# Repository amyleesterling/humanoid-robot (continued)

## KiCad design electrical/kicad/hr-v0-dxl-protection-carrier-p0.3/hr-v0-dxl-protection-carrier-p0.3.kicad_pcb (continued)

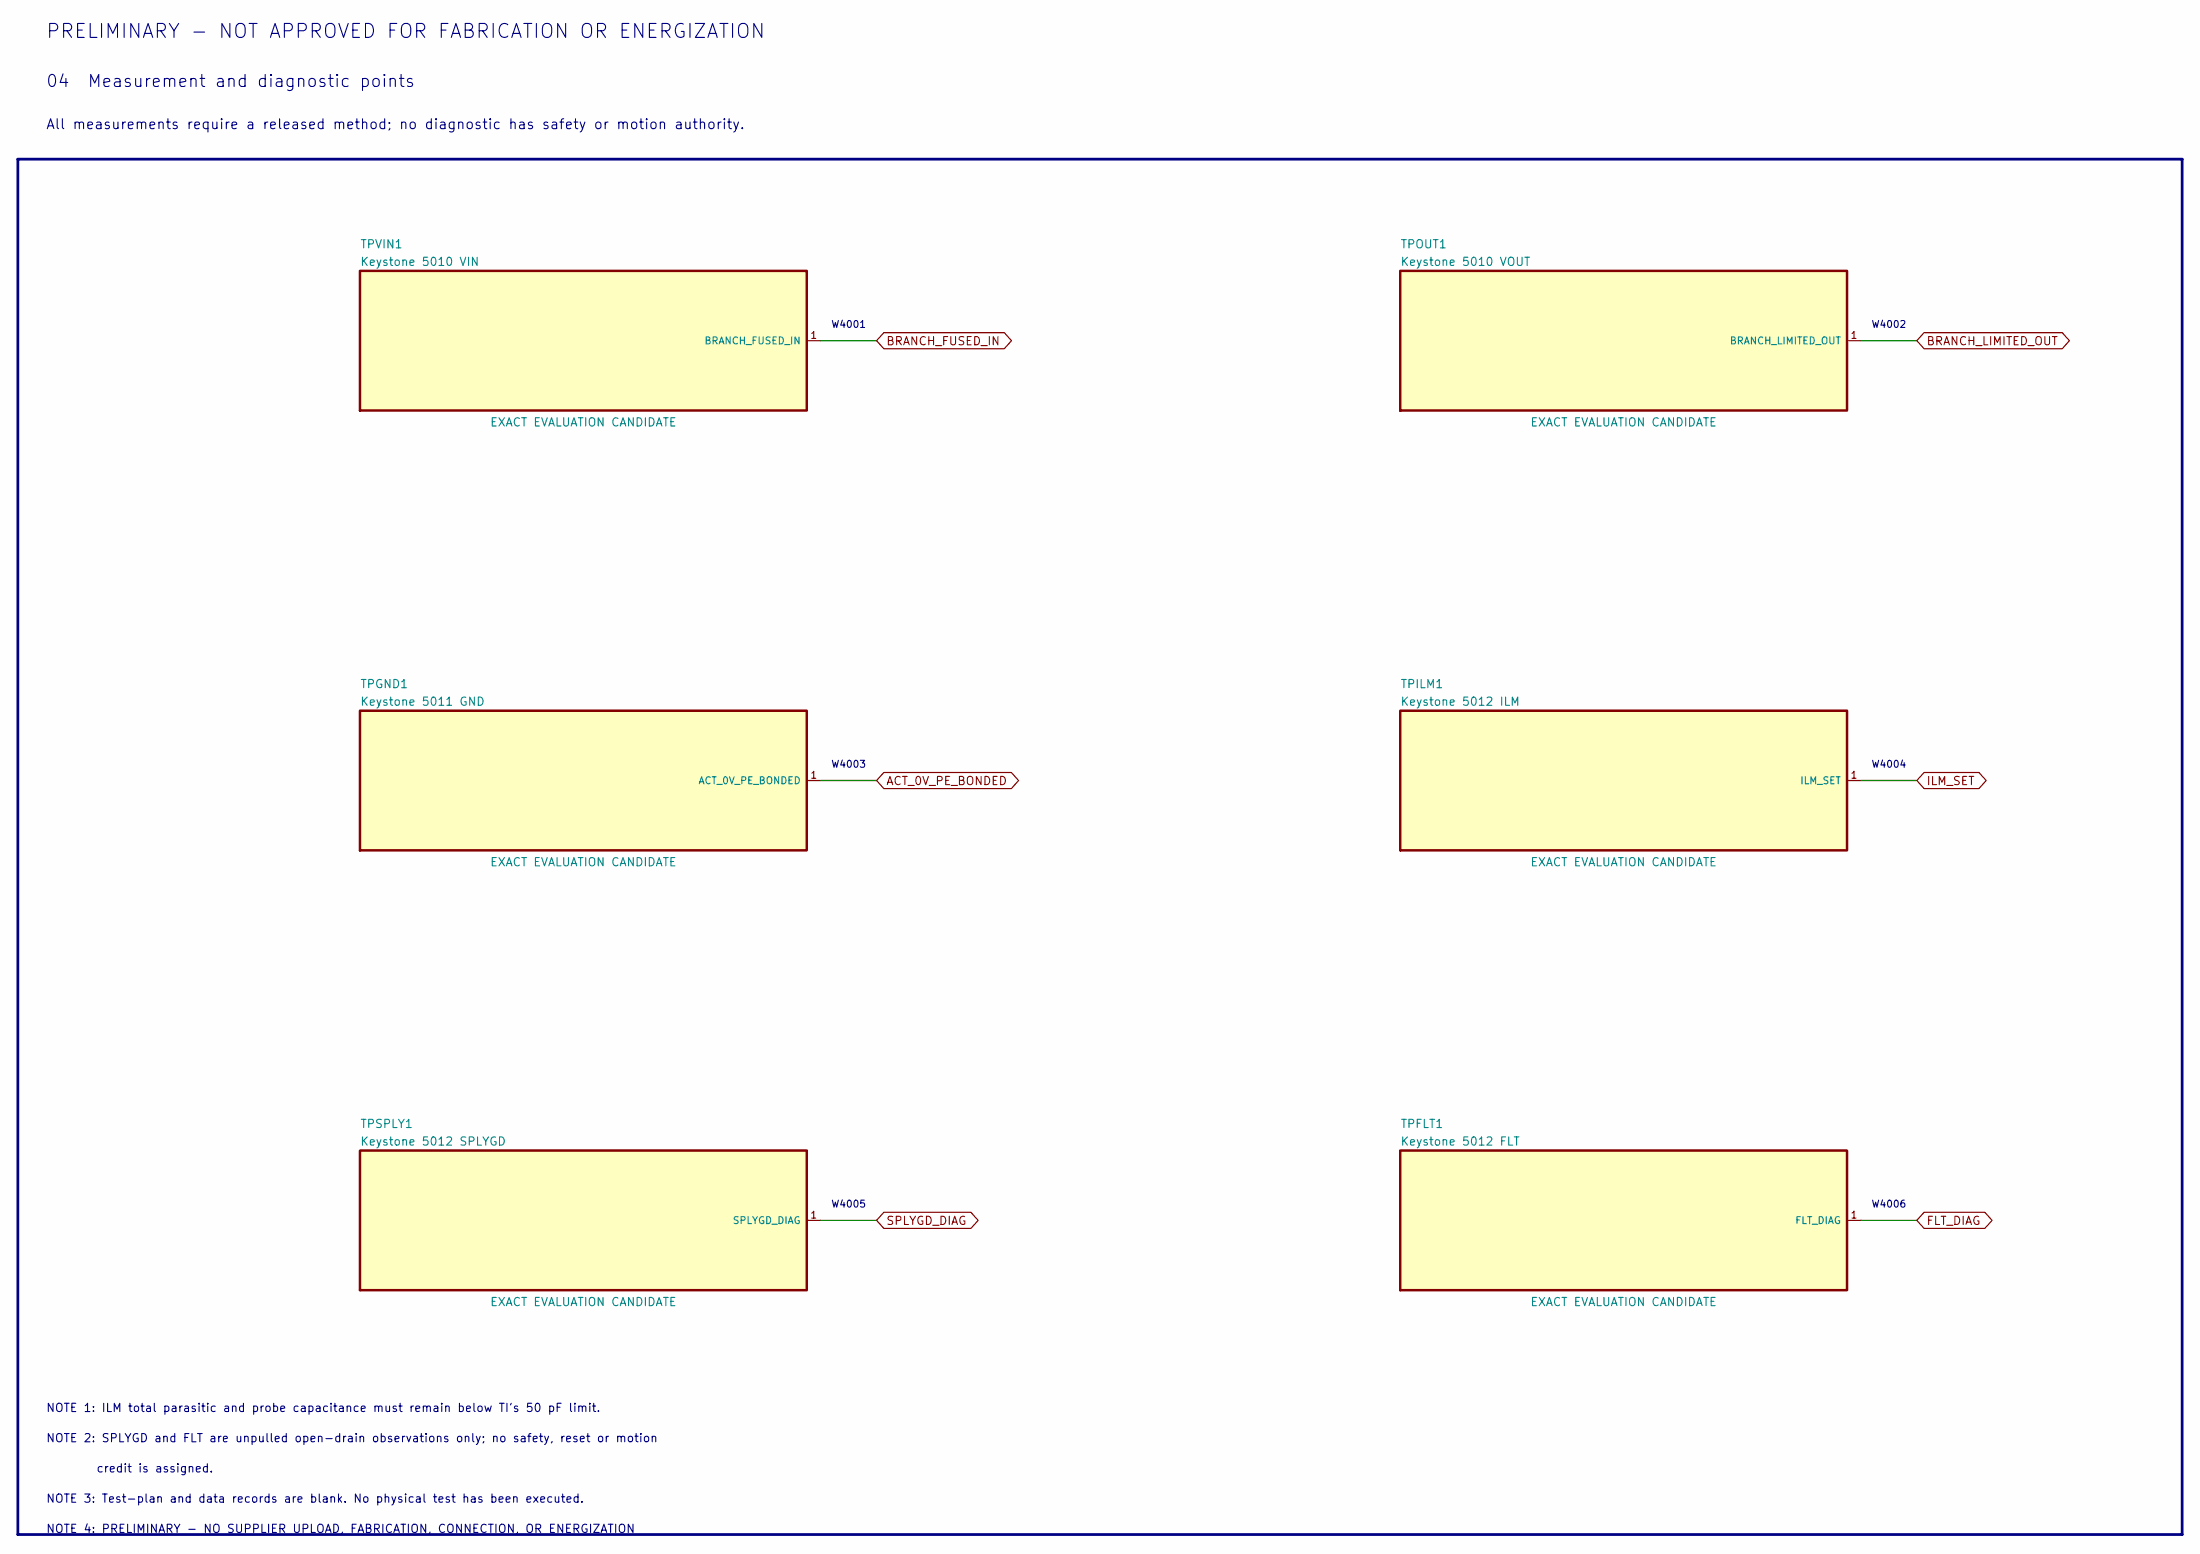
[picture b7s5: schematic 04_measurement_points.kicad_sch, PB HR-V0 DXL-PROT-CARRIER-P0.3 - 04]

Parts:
TPFLT1: Keystone 5012 FLT; TestPoint_Keystone_5010-5014_Multipurpose
TPGND1: Keystone 5011 GND; TestPoint_Keystone_5010-5014_Multipurpose
TPILM1: Keystone 5012 ILM; TestPoint_Keystone_5010-5014_Multipurpose
TPOUT1: Keystone 5010 VOUT; TestPoint_Keystone_5010-5014_Multipurpose
TPSPLY1: Keystone 5012 SPLYGD; TestPoint_Keystone_5010-5014_Multipurpose
TPVIN1: Keystone 5010 VIN; TestPoint_Keystone_5010-5014_Multipurpose

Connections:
ACT_0V_PE_BONDED: TPGND1.1; also elsewhere on the board
BRANCH_FUSED_IN: TPVIN1.1; also elsewhere on the board
BRANCH_LIMITED_OUT: TPOUT1.1; also elsewhere on the board
FLT_DIAG: TPFLT1.1; also elsewhere on the board
ILM_SET: TPILM1.1; also elsewhere on the board
SPLYGD_DIAG: TPSPLY1.1; also elsewhere on the board

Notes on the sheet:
PRELIMINARY - NOT APPROVED FOR FABRICATION OR ENERGIZATION
04 Measurement and diagnostic points
All measurements require a released method; no diagnostic has safety or motion authority.
W4001
W4002
W4003
W4004
W4005
W4006
NOTE 1: ILM total parasitic and probe capacitance must remain below TI's 50 pF limit.
NOTE 2: SPLYGD and FLT are unpulled open-drain observations only; no safety, reset or motion
credit is assigned.
NOTE 3: Test-plan and data records are blank. No physical test has been executed.
NOTE 4: PRELIMINARY - NO SUPPLIER UPLOAD, FABRICATION, CONNECTION, OR ENERGIZATION

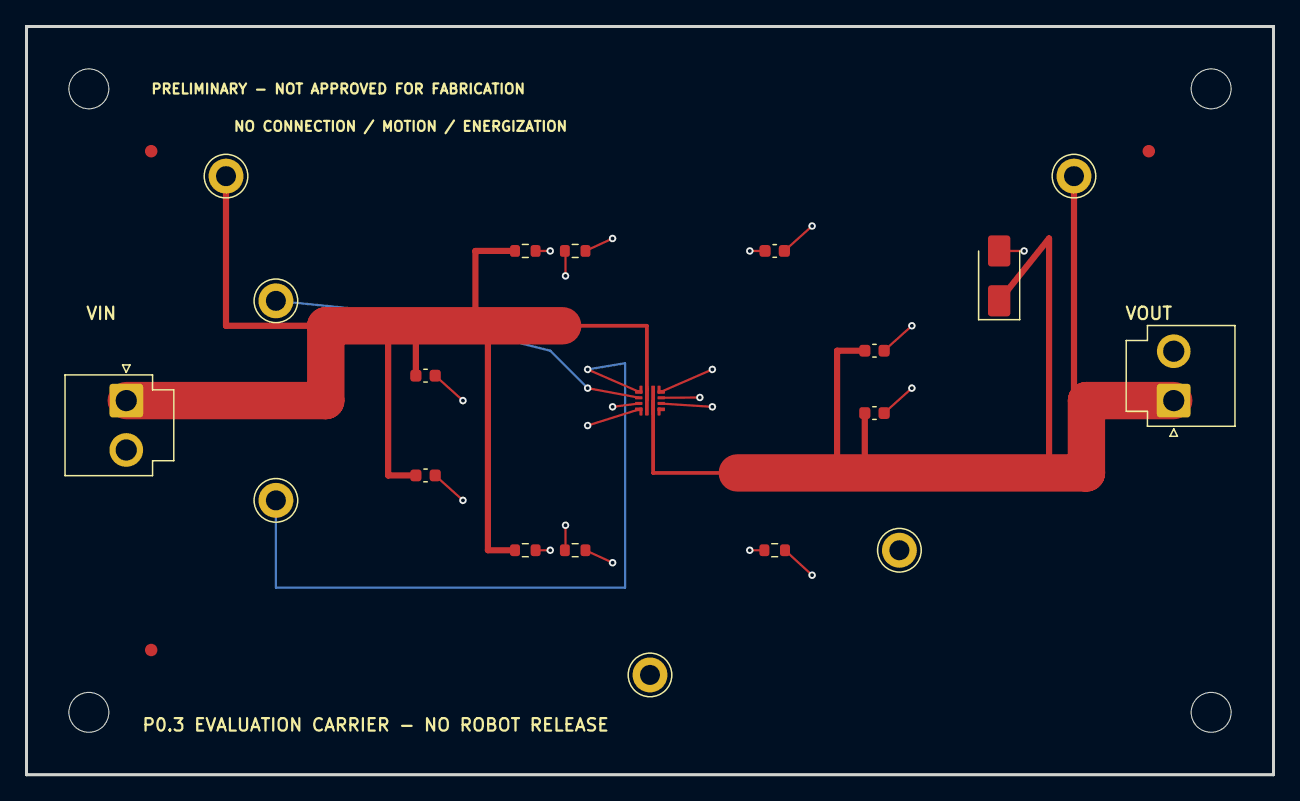
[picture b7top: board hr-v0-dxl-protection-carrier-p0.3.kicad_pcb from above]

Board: 4 copper layers, 100.0 x 60.0 mm, 27 parts (0 on the bottom side), 9 nets.

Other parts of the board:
FD1, FD2, FD3: BOARD-LEVEL GLOBAL FIDUCIAL 1.0/2.0 mm; PROVIDER 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
MH1, MH2, MH3, MH4: BOARD-ONLY M3; MOUNTING SELECTION REQUIRED; MountingHole_3.2mm_M3
